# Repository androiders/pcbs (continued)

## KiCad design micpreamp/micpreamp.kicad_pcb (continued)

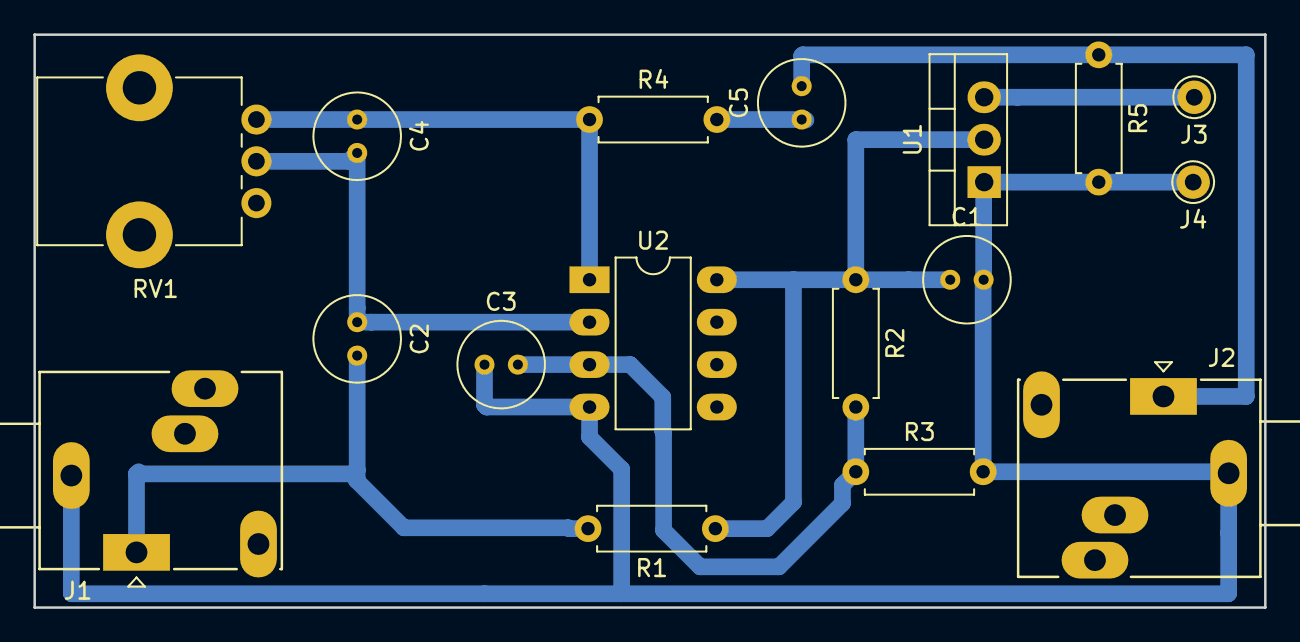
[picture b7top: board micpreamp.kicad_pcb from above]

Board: 2 copper layers, 73.7 x 34.3 mm, 17 parts (0 on the bottom side), 9 nets.

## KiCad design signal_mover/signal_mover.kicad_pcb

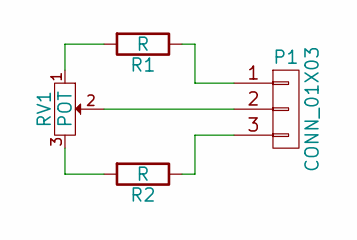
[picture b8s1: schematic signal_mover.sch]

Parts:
P1: CONN_01X03; PinSocket_1x03_P2.54mm_Vertical
R1, R2: R; R_Axial_DIN0207_L6.3mm_D2.5mm_P7.62mm_Horizontal
RV1: POT; Potentiometer_Piher_PC-16_Single_Vertical

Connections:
unnamed: P1.1, R1.1
unnamed: P1.2, RV1.2
unnamed: P1.3, R2.1
unnamed: R1.2, RV1.1
unnamed: R2.2, RV1.3

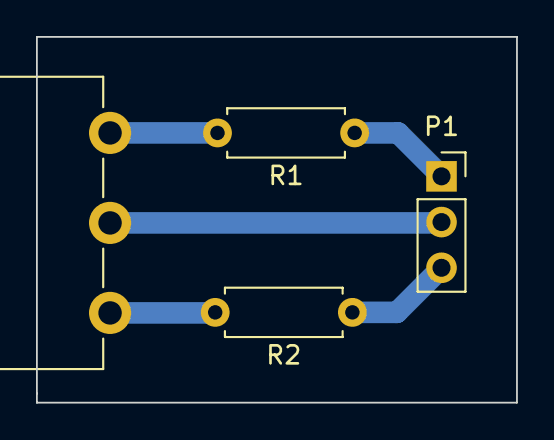
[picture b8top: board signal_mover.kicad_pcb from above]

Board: 2 copper layers, 26.7 x 20.3 mm, 4 parts (0 on the bottom side), 5 nets.

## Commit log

2018-06-18 added pcb files for projescts
2018-06-18 updates, added brewer
2018-06-19 added new gcode
2018-06-19 updated ocb to NOT use copper fill in kicad. This makes better geometry in flatcam!
2018-06-19 updated isolation cut depth to -0.08
2018-06-27 update readme and added flatcam defaults file
2018-06-27 layout
2018-09-29 added pwr supply
2018-09-29 updated standard settings
2018-09-29 added pwr supply gerber and gcode
2018-09-29 updated flatcamd efaults
2018-09-30 updatd flatcam settings
2018-10-15 added signa, mover smll pcb and gcode, gerber etc
2018-10-16 updated signal mover
2018-10-29 added mic preamp files
2018-10-29 added mic preamp cutout gcode
2018-10-29 updated flatcam defaults
2018-10-29 added files
2018-11-05 added tiny spi proj and fixed an error with the mic preamp
2018-11-21 Backlink to CADLAB.io has been added.
2018-11-26 added distpedal files
2019-04-03 added stuff
2019-04-06 added gcode for distpesal
2019-04-30 added pedal board gcode for 6.3 mm jacks
2019-05-01 gcode for pedal board
2019-05-04 updated connector gcode
2020-04-25 added numitron clock files
2020-10-20 addded smps-B_Cu.gbr
2022-01-06 removed wrong version
2022-01-06 some updates
2022-01-09 added h bridge
2022-03-15 work on numitron
2022-08-30 added files for mc unit
2022-08-30 added files for numitron clock
